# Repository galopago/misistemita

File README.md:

# MISISTEMITA

## ELECTRONIC HARDWARE PROTOTYPING SYSTEM. SOLDERLESS, ROBUST AND OPEN SOURCE

Electronic hardware prototyping system. Solderless, robust and open source. Solves the typical problem of the circuit that works on a breadboard but stops working on a real-world setup. Easy to replicate and compatible with virtually every electronic module.

From this!                     |To this!                              |
-------------------------------|--------------------------------------|
||

Read this in other languages: [Español](/assets/markdown/README.es.md)

The system is completely open source, all the files required to create your own system (schematics, PCB, templates, etc.) are available for download.

### Build a working project in 5 steps:

1.Component selection          |2.Position the components on the backplate |
-------------------------------|-------------------------------------------|
|     |

3.Wire and program           |4.Attach backplate to the enclosure |
-----------------------------|-----------------------------------|
|    |

5.Close lid and install on the wall  |
------------------------------------------|
        |

## System components

The prototyping system is built around 3 key components:
* Backplates
* Electronic boards
* Waterproof enclosures

Backplates                     | Electronic boards                     | Waterproof enclosures       |
-------------------------------|---------------------------------------|---------------------------------------|
| | |

## BACKPLATES

Backplates are flat plates with a distance between holes of 10.16 mm. Backplates are classified as follows: backplates fixed to the enclosure and mechanical adapters for other kinds of modules. The backplates are made in PCB houses, however, they can be built with other materials and processes like laser cutting, CNC machining or homemade with drill and saw!.
[Source files for backplates](/a-backplates)

### Backplates - fixed to the enclosure

This kind of backplates is fixed to the enclosure, all compatible boards are placed on it. The fixing of the backplate to the enclosure is done with self-tapping screws

Backplates - fixed to the enclosure   | 
----------------------------------------------------|
|

### Backplates - mechanical adapter

This kind of adapters are used to convert modules that have mounting holes, but not compatible with 10.16 mm

Backplates - mechanical adapter                      | Backplates - mechanical adapter installed on panel     | 
-----------------------------------------------------|------------------------------------------------------|
||

The distance between holes of 10.16 mm was found after experimentation, using an universal PCB with 2.54 mm space between holes. The 3 mm of diameter was chosen because it is a very  common hole diameter in electronic modules found online)

Distance test between holes 5.08, 7.62 y 10.16mm | Distance test between holes 5.08, 7.62 y 10.16 mm with nuts | 
-----------------------------------------------------|------------------------------------------------------|
||

10.16 mm of distance between holes is a good compromise between compactness and ease of attachment of accessories. Given that the distance of 10.16 mm is an integer multiple of 2.54 mm, these panels could be homebuilt with universal PCB 

Backplate made of universal PCB  | Backplate made of plastic sheet and hand drilled | 
-----------------------------------------------------|------------------------------------------------------|
||

### Fixing elements

Different types of fixing elements for securing boards to backplate |
-----------------------------------------------------|
|

To secure boards to backplate (leaving some gap to avoid shortcuts), there are many possibilities like:

### Nylon spacer, reverse locking without screws

This is a single piece element that allows to attach the boards to the backplate without tools, to detach them a pliers are required

Nylon spacer on board | Board attached to the backplate           | spacer from below  |
---------------------------------|---------------------------------------|---------------------------------------|
| | |

### Nylon spacer with screw and nut

This element is composed of 3 pieces: spacer, screw and nut. A screwdriver is required for fastening and detachment

Nylon spacer with screw on board | Board attached to the backplate             | Nylon spacer with nut from below  |
---------------------------------|---------------------------------------|---------------------------------------|
| | |

### Metal spacer with screw and nut

This element is composed of 3 pieces: spacer, screw and nut. A screwdriver is required for fastening and detachment

Metal spacer with screw on board  | Board attached to the backplate           | Metal spacer with nut from below  |
---------------------------------|---------------------------------------|---------------------------------------|
| | |

## ELECTRONIC BOARDS

Electronic boards are classified as follows:screw terminal connectors, breakouts and active boards. Screw terminals are used as a means of interconnection between all of them, because they work pretty well for solid wire and stranded cable, in addition no crimping is needed. Another good point is that many wires can be attached to the same terminal, very helpful for connecting wire jumpers.

### electronic boards - screw terminal connectors

This type of board is used as a connection point to the external world, organizing in the same spot, sensor inputs, outputs and power sources. Helpful to provide multiple VCC and GND connection points using wire jumpers. They also have holes compatible with 10.16 mm pitch backplates.
[Source files for screw terminal connectors](/b-screw-terminal-wire-connectors)

screw terminal connectors - Different types  |screw terminal connectors - unified spot for cable ingress |  screw terminal connectors - wire diversity|
------------------------|-------------------------------------------------------------|-----------------------------------------------------------|
|| |

### electronic boards - breakouts

This type of board is used to convert DIL style electronic modules into screw terminals, they also have holes compatible with 10.16 mm pitch backplates.
[Source files for breakouts](/c-breakouts)

breakouts - Different types               | breakouts - breakout for Arduino Nano            | breakouts - module as a part of a project |
------------------------------------------|---------------------------------------------------|--------------------------------------------|
|||

### electronic boards - active boards

This type of board has some electrical/electronic component soldered in to do a specific function.
[Source files for active boards](/d-electronics)

electronic boards - Different types       | electronic boards - AC/DC  power supply      | electronic boards - module as a part of a project |
------------------------------------------|---------------------------------------------------|--------------------------------------------|
|||

Same as homebuilt backplates, electronic boards also could be manufactured in a similar fashion, as long as screw terminals were used and mounting holes in increments of 10.16 mm were drilled

homebuilt compatible electronic boards | hybrid project mixing industrial and homebuilt boards | hybrid project installed and working|
------------------------------------------|---------------------------------------------------|--------------------------------------------|
|||

## WATERPROOF ENCLOSURES

The system is based on waterproof enclosures with the following characteristics:
* shall have mounting bosses for the PCB or backplate.
* must be able to be mounted on the wall without drilling the enclosure

### waterproof enclosures - mounting bosses for the PCB using self-tapping screws

The enclosures shall have mounting bosses where the backplate will be attached using self-tapping screws. Those holes usually came pre-drilled and should not break the enclosure

mounting bosses for the PCB |
--------------------------------------------|
|

### waterproof enclosures - wall mount without enclosure drilling

The enclosures must have external mounting ears. There are other kind of boxes that have some holes in the back for mounting purposes, but those holes do not break in the enclosure. In this particular case, some additional accessories will be required.

waterproof enclosures with several wall mounting methods|
-----------------------------------------------------|
               |

waterproof enclosures with mounting ears fixed directly to the wall with screws |
-------------------------------------------------------------------|
                          |

### Fixing accessories

For enclosures with mounting holes in the back, some picture hanging accessories will be handy for mounting them.

Accessories for wall hanging pictures, flat and Z-shaped |
---------------------------------------------------------|
                |

flat hanging accessories | detail of flat hanging accessories  | project using flat hanging accessories for mounting|
------------------------------------------|---------------------------------------------------|--------------------------------------------|
|||

Z-shaped hanging accessories | detail of Z-shaped hanging accessories | project using Z-shaped hanging accessories for mounting|
------------------------------------------|---------------------------------------------------|--------------------------------------------|
|||

### Cable ingress accessories

To avoid moisture and dust infiltration in the enclosure at the cable entry point, this system uses two alternatives:
* Cable glands
* Panel mount connectors

### Cable glands

Cable glands limit the amount of dust and moisture that can enter the enclosure at the cable entry point. Additionally, they provide strain support, avoiding internal disconnections. Cable glands were available in many sizes according to cable thickness. Usually they were used in permanent installations, because the enclosure has to be opened to disconnect the cables.

Different types of cable glands | holes for cable glands installation | Power and signal cables through cable glands|
------------------------------------------|---------------------------------------------------|--------------------------------------------|
|||

### Panel mount connectors

Panel mount connectors limit the amount of dust and moisture that can enter the enclosure at the cable entry point. Additionally, they provide strain support, avoiding internal disconnections.Usually they were used when wires need to be disconnected frequently. Sometimes soldering or crimping is required.

Sample of some types of panel mount connectors | USB-B and aviation panel mount connectors | Power and signal cables through panel mount connectors|
------------------------------------------|---------------------------------------------------|--------------------------------------------|
|||

# Files and additional info:

| DESCRIPTION                                                     | LINK                                   
|-----------------------------------------------------------------|----------------------------------------------------------------------
| Source files for backplates                                     | [Backplates](/a-backplates)
| Source files for screw terminal connectors                      | [Screw terminal connectors](/b-screw-terminal-wire-connectors)
| Source files for breakouts                                      | [Breakout](/c-breakouts)
| Source files for active boards                                  | [Active boards](/d-electronics)
| Complete finished examples using Misistemita                    | [Galopago](https://galopago.github.io)

Misistemita is an open source project by [Galopago](https://galopago.github.io/)

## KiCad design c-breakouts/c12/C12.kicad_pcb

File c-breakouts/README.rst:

=======================================================================================================================================
TUSISTEMITA TYPE-C BOARDS: BREAKOUTS
=======================================================================================================================================

Breakout for converting electronic modules, to screw terminal connectors and 10.16 mm hole spacing

Directory structure of every board folder
--------------------------------------------------------------------------
* The root contains KiCad files: project, schematic and PCB.
* gerber/single directory contains ready to manufacture files, for a single board.
* gerber/panel_100mmx100mm directory contains ready to manufacture files that fits in a 100mm x 100mm panel (use Vcuts!).

========  ===============  ============== 
FOLDER    PCB MARK         DESCRIPTION
========  ===============  ============== 
C00       C00_BREAKOUT     Breakout for power meter PZEM-004T-100A (V3.0)
C01       C01_BREAKOUT     Breakout for RAK811 LoRa breakboard
C02       C02_BREAKOUT     Breakout for RAK4200 LoRa breakboard
C03       C03_BREAKOUT     Breakout for 2xAA R6 type batteries
C04       C04_BREAKOUT     Breakout for Arduino Nano
C05       C05_BREAKOUT     Breakout for Raspberry Pi 40 pin (2x20) header
C06       C06_BREAKOUT     Breakout for 21 mm x 23 mm prototyping area
C07       C07_BREAKOUT     Breakout for ESP32 devboards with 38 pins (2x19 2.54mm pitch) or less and 25,4 mm separation between headers  
C08       C08_BREAKOUT     Breakout for ESP8266 devboards with 30 pins (2x15 2.54mm pitch) or less and ( 22,86 or 27.94mm ) separation between headers  
C09       C09_BREAKOUT     Breakout for USB A Male (USB A Female connected to screw terminals) power pins
C10       C10_BREAKOUT     Breakout for 0.96" OLED 4 pin I2C display
C11       C11_BREAKOUT     Breakout for Raspberry Pi Pico Board
C12       C12_BREAKOUT     Breakout for ESP32 Cam Board
C13       C13_BREAKOUT     Breakout for 18 pin (2x9) header
========  ===============  ==============

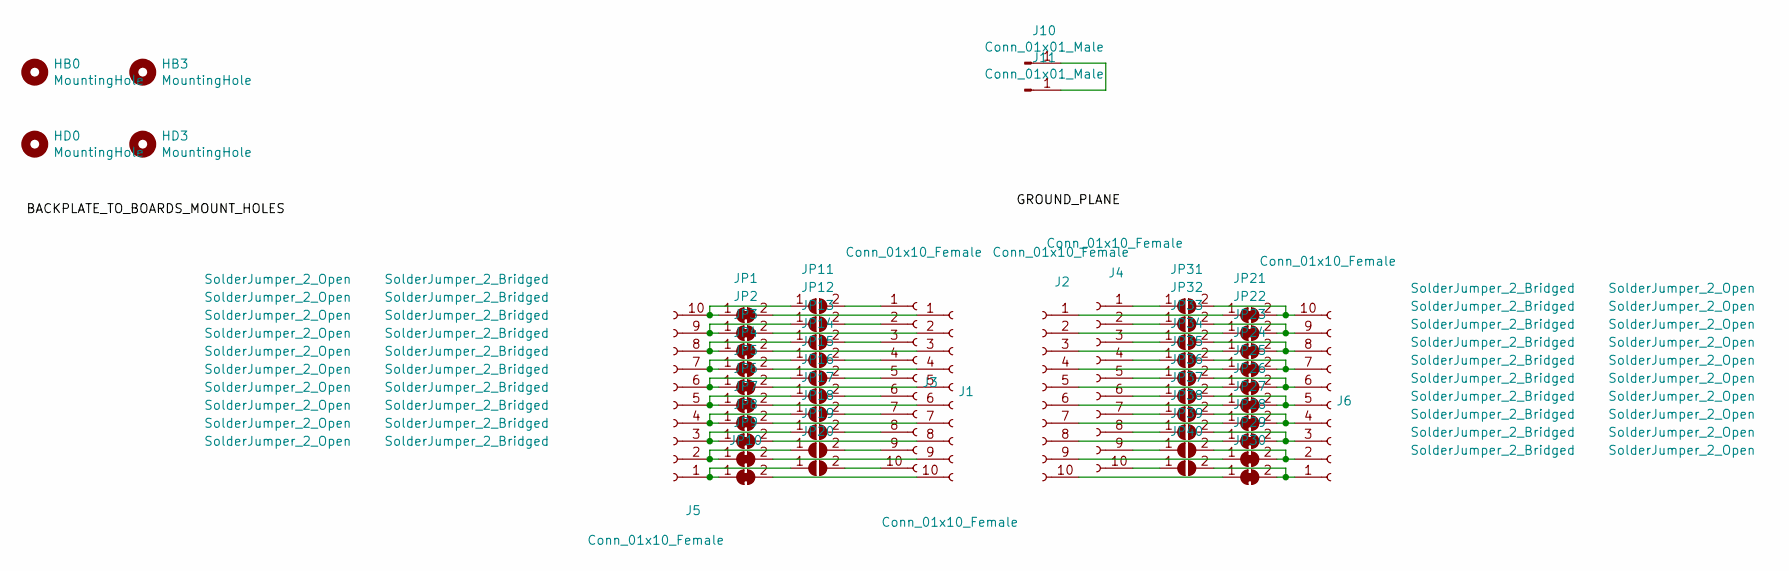
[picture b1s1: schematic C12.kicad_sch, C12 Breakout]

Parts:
HB0, HB3: MountingHole; MountingHole_3mm
HD0, HD3: MountingHole; MountingHole_3mm
J1, J2, J3, J4: Conn_01x10_Female; PinHeader_1x10_P2.54mm_Vertical
J5, J6: Conn_01x10_Female; TerminalBlock_4Ucon_1x10_P3.50mm_Vertical
J10, J11: Conn_01x01_Male; SolderWirePad_1x01_Drill1mm
JP1, JP2, JP3, JP4, JP5, JP6, JP7, JP8, JP9, JP10, JP21, JP22, JP23, JP24, JP25, JP26, JP27, JP28, JP29, JP30: SolderJumper_2_Bridged; SolderJumper-2_P1.3mm_Bridged_RoundedPad1.0x1.5mm
JP11, JP12, JP13, JP14, JP15, JP16, JP17, JP18, JP19, JP20, JP31, JP32, JP33, JP34, JP35, JP36, JP37, JP38, JP39, JP40: SolderJumper_2_Open; SolderJumper-2_P1.3mm_Open_RoundedPad1.0x1.5mm

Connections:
unnamed: J1.1, JP1.2 (B)
unnamed: J1.2, JP2.2 (B)
unnamed: J1.3, JP3.2 (B)
unnamed: J1.4, JP4.2 (B)
unnamed: J1.5, JP5.2 (B)
unnamed: J1.6, JP6.2 (B)
unnamed: J1.7, JP7.2 (B)
unnamed: J1.8, JP8.2 (B)
unnamed: J1.9, JP9.2 (B)
unnamed: J1.10, JP10.2 (B)
unnamed: J2.1, JP21.1 (A)
unnamed: J2.2, JP22.1 (A)
unnamed: J2.3, JP23.1 (A)
unnamed: J2.4, JP24.1 (A)
unnamed: J2.5, JP25.1 (A)
unnamed: J2.6, JP26.1 (A)
unnamed: J2.7, JP27.1 (A)
unnamed: J2.8, JP28.1 (A)
unnamed: J2.9, JP29.1 (A)
unnamed: J2.10, JP30.1 (A)
unnamed: J3.1, JP11.2 (B)
unnamed: J3.2, JP12.2 (B)
unnamed: J3.3, JP13.2 (B)
unnamed: J3.4, JP14.2 (B)
unnamed: J3.5, JP15.2 (B)
unnamed: J3.6, JP16.2 (B)
unnamed: J3.7, JP17.2 (B)
unnamed: J3.8, JP18.2 (B)
unnamed: J3.9, JP19.2 (B)
unnamed: J3.10, JP20.2 (B)
unnamed: J4.1, JP31.1 (A)
unnamed: J4.2, JP32.1 (A)
unnamed: J4.3, JP33.1 (A)
unnamed: J4.4, JP34.1 (A)
unnamed: J4.5, JP35.1 (A)
unnamed: J4.6, JP36.1 (A)
unnamed: J4.7, JP37.1 (A)
unnamed: J4.8, JP38.1 (A)
unnamed: J4.9, JP39.1 (A)
unnamed: J4.10, JP40.1 (A)
unnamed: J10.1, J11.1
unnamed: J5.10, JP1.1 (A), JP11.1 (A)
unnamed: J5.1, JP10.1 (A), JP20.1 (A)
unnamed: J5.9, JP2.1 (A), JP12.1 (A)
unnamed: J5.8, JP3.1 (A), JP13.1 (A)
unnamed: J5.7, JP4.1 (A), JP14.1 (A)
unnamed: J5.6, JP5.1 (A), JP15.1 (A)
unnamed: J5.5, JP6.1 (A), JP16.1 (A)
unnamed: J5.4, JP7.1 (A), JP17.1 (A)
unnamed: J5.3, JP8.1 (A), JP18.1 (A)
unnamed: J5.2, JP9.1 (A), JP19.1 (A)
unnamed: J6.10, JP21.2 (B), JP31.2 (B)
unnamed: J6.9, JP22.2 (B), JP32.2 (B)
unnamed: J6.8, JP23.2 (B), JP33.2 (B)
unnamed: J6.7, JP24.2 (B), JP34.2 (B)
unnamed: J6.6, JP25.2 (B), JP35.2 (B)
unnamed: J6.5, JP26.2 (B), JP36.2 (B)
unnamed: J6.4, JP27.2 (B), JP37.2 (B)
unnamed: J6.3, JP28.2 (B), JP38.2 (B)
unnamed: J6.2, JP29.2 (B), JP39.2 (B)
unnamed: J6.1, JP30.2 (B), JP40.2 (B)

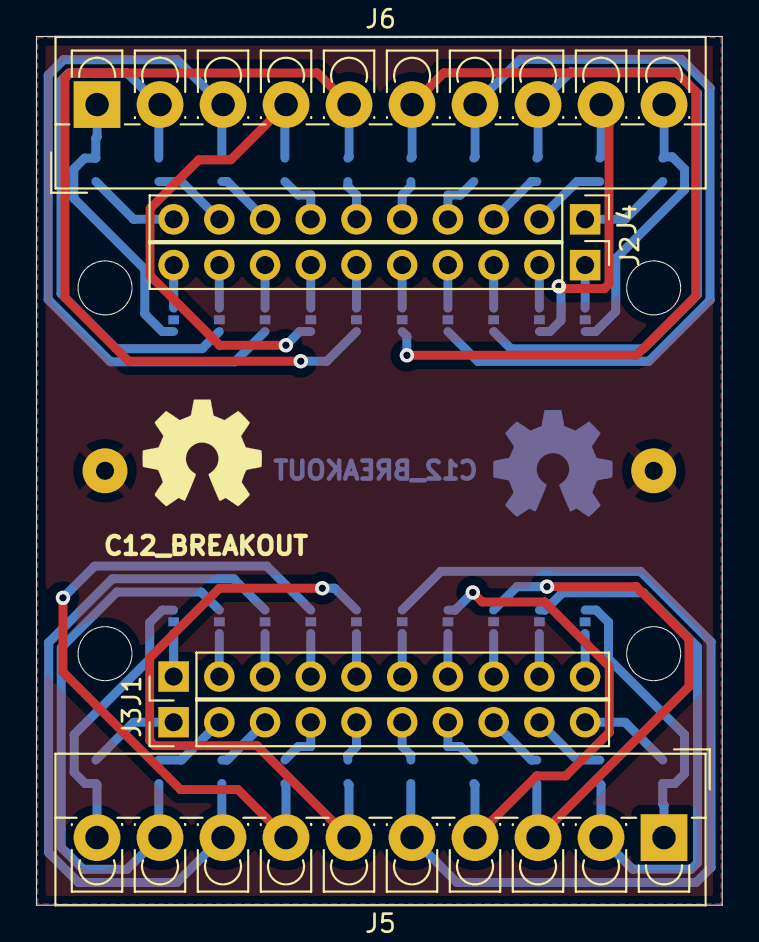
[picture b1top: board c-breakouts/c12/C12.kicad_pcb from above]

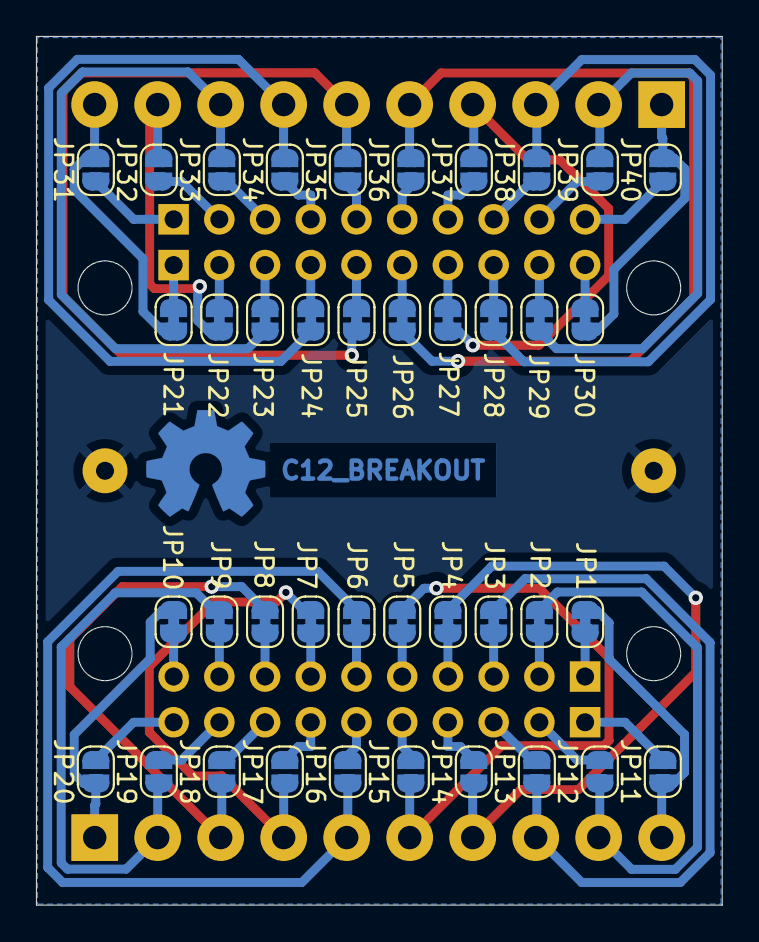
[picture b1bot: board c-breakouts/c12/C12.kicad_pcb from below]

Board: 2 copper layers, 38.1 x 48.3 mm, 54 parts (41 on the bottom side), 61 nets.

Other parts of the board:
REFS0**: OSHW-Symbol_6.7x6mm_Copper
REFS1**: OSHW-Symbol_6.7x6mm_SilkScreen

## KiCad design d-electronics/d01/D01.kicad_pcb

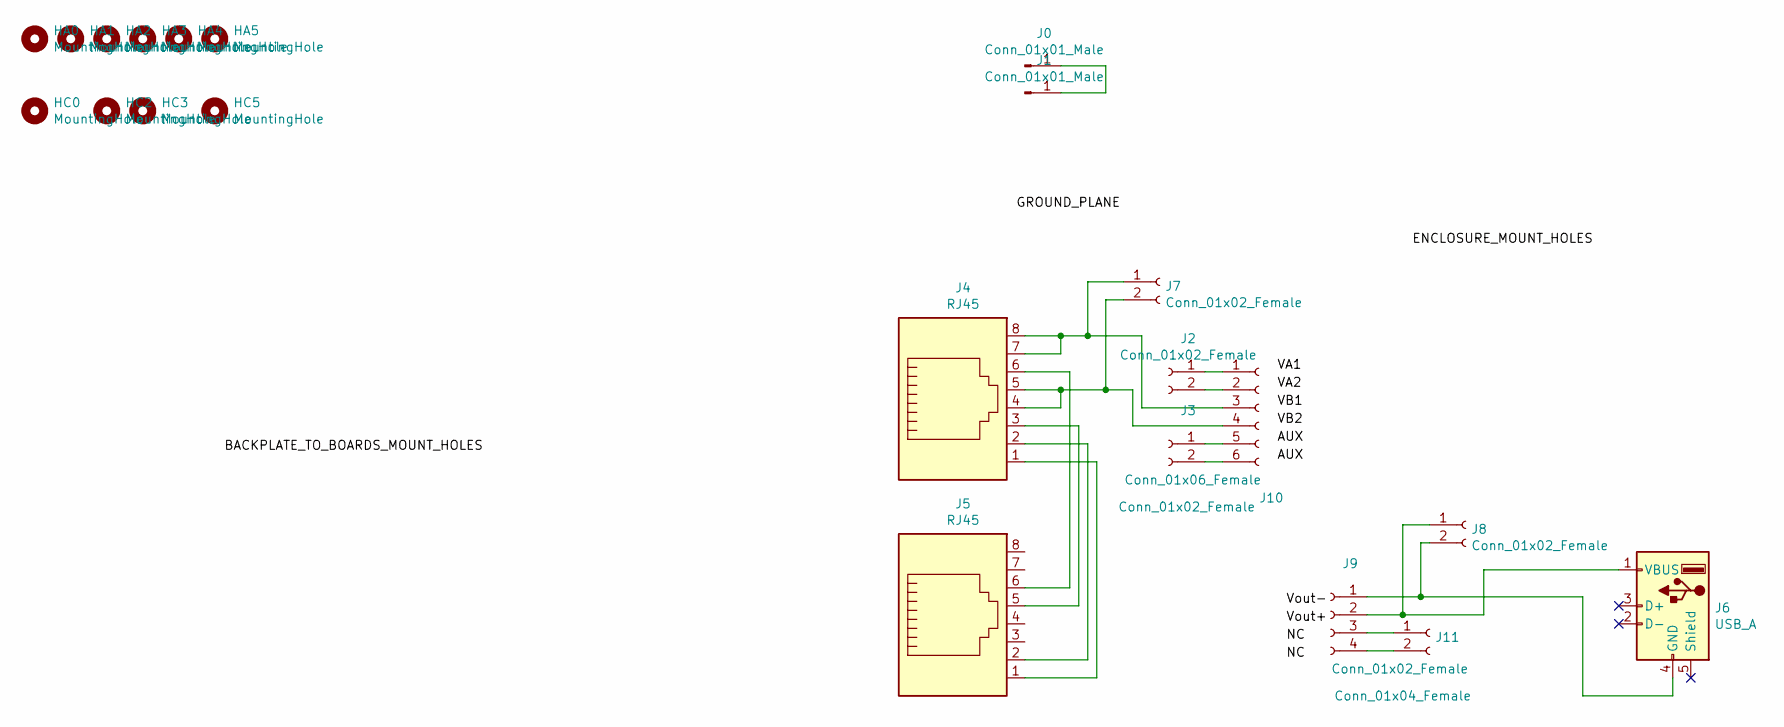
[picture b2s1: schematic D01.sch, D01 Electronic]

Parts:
HA0, HA1, HA2, HA3, HA4, HA5: MountingHole; MountingHole_3mm
HC0, HC2, HC3, HC5: MountingHole; MountingHole_3mm
J0, J1: Conn_01x01_Male; SolderWirePad_1x01_Drill1mm
J2, J3, J11: Conn_01x02_Female; PinSocket_1x02_P2.54mm_Vertical
J4, J5: RJ45; RJ45_Wayconn_MJEA-880X1_Horizontal
J6: USB_A; USB_A_Stewart_SS-52100-001_Horizontal
J7, J8: Conn_01x02_Female; TerminalBlock_4Ucon_1x02_P3.50mm_Horizontal
J9: Conn_01x04_Female; PinSocket_1x04_P2.54mm_Vertical
J10: Conn_01x06_Female; PinSocket_1x06_P2.54mm_Vertical

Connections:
unnamed: J0.1, J1.1
unnamed: J4.1, J5.1
unnamed: J4.2, J5.2
unnamed: J4.3, J5.5
unnamed: J4.6, J5.6
unnamed: J6.1 (VBUS), J8.1, J9.2
unnamed: J6.4 (GND), J8.2, J9.1
unnamed: J2.1, J10.1
unnamed: J2.2, J10.2
unnamed: J4.7, J4.8, J7.1, J10.3
unnamed: J4.4, J4.5, J7.2, J10.4
unnamed: J3.1, J10.5
unnamed: J3.2, J10.6
unnamed: J9.3, J11.1
unnamed: J9.4, J11.2

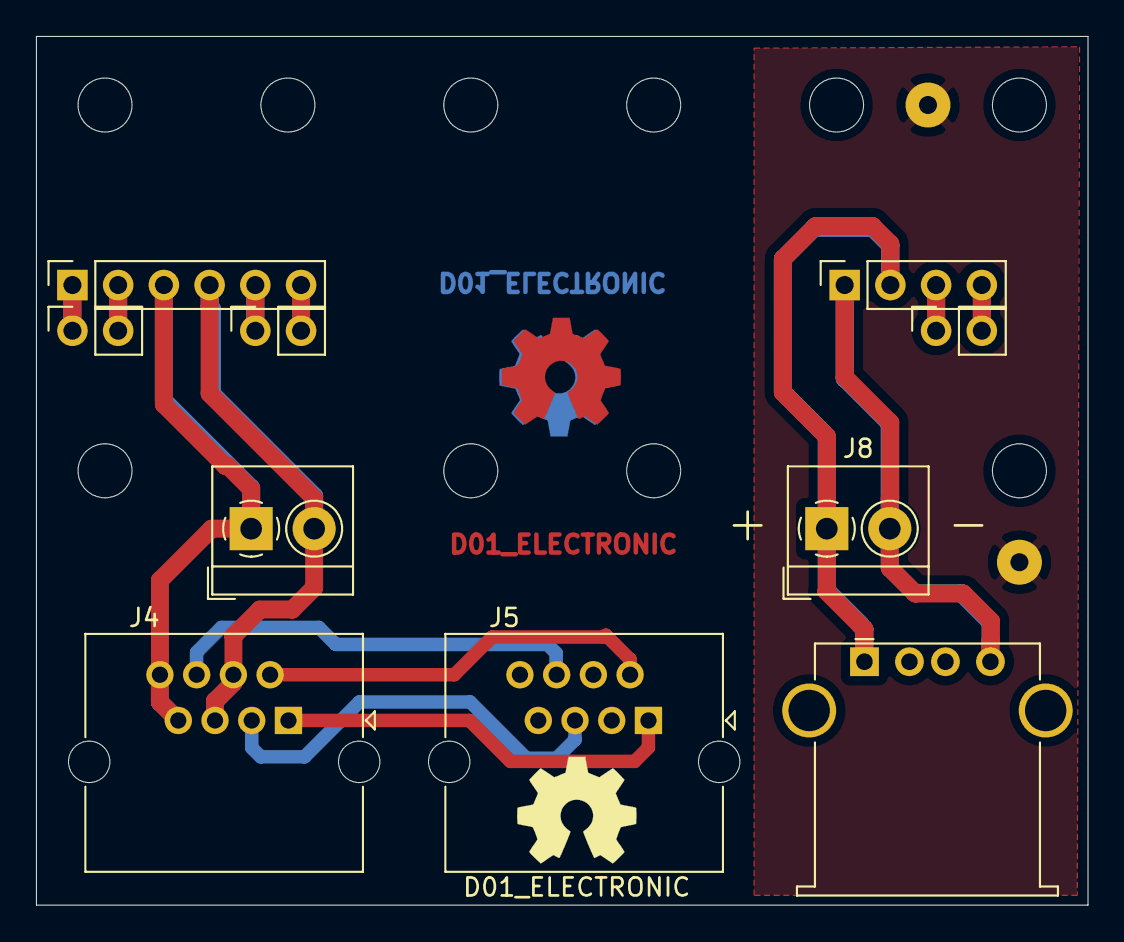
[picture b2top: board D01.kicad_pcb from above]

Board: 2 copper layers, 58.4 x 48.3 mm, 22 parts (0 on the bottom side), 15 nets.

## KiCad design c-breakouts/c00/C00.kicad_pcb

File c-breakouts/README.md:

# MISISTEMITA TYPE-C BOARDS: BREAKOUTS

Breakout for converting electronic modules, to screw terminal connectors and 10.16 mm hole spacing

Different breakout boards                                           |
------------------------------------------------------------------------------------|
|

## Directory structure of every board folder

* The root contains KiCad files: project, schematic and PCB.
* gerber/single directory contains ready to manufacture files, for a single board.
* gerber/panel_100mmx100mm directory contains ready to manufacture files that fits in a 100mm x 100mm panel (use Vcuts!).
* assets folder contains support files for readme.md

| DESCRIPTION                                    | PCB MARK     | LINK                                     
|------------------------------------------------|--------------|------
| Breakout for power meter PZEM-004T-100A (V3.0) | C00_BREAKOUT | [c00](/c-breakouts/c00)
| Breakout for RAK811 LoRa breakboard            | C01_BREAKOUT | [c01](/c-breakouts/c01)
| Breakout for RAK4200 LoRa breakboard           | C02_BREAKOUT | [c02](/c-breakouts/c02)
| Breakout for 2xAA R6 type batteries            | C03_BREAKOUT | [c03](/c-breakouts/c03)
| Breakout for Arduino Nano                      | C04_BREAKOUT | [c04](/c-breakouts/c04)
| Breakout for Raspberry Pi 40 pin (2x20) header | C05_BREAKOUT | [c05](/c-breakouts/c05)
| Breakout for 21 mm x 23 mm prototyping area    | C06_BREAKOUT | [c06](/c-breakouts/c06)
| Breakout for ESP32 devboards with 38 pins (2x19 2.54mm pitch) or less and 25,4 mm separation between headers                | C07_BREAKOUT | [c07](/c-breakouts/c07) 
| Breakout for ESP8266 devboards with 30 pins (2x15 2.54mm pitch) or less and ( 22,86 or 27.94mm ) separation between headers | C08_BREAKOUT | [c08](/c-breakouts/c08)
| Breakout for USB A Male (USB A Female connected to screw terminals) power pins | C09_BREAKOUT | [c09](/c-breakouts/c09)
| Breakout for 0.96" OLED 4 pin I2C display      | C10_BREAKOUT | [c10](/c-breakouts/c10)
| Breakout for Raspberry Pi Pico Board           | C11_BREAKOUT | [c11](/c-breakouts/c11)
| Breakout for ESP32 Cam Board                   | C12_BREAKOUT | [c12](/c-breakouts/c12)
| Breakout for 18 pin (2x9) header               | C13_BREAKOUT | [c13](/c-breakouts/c13)

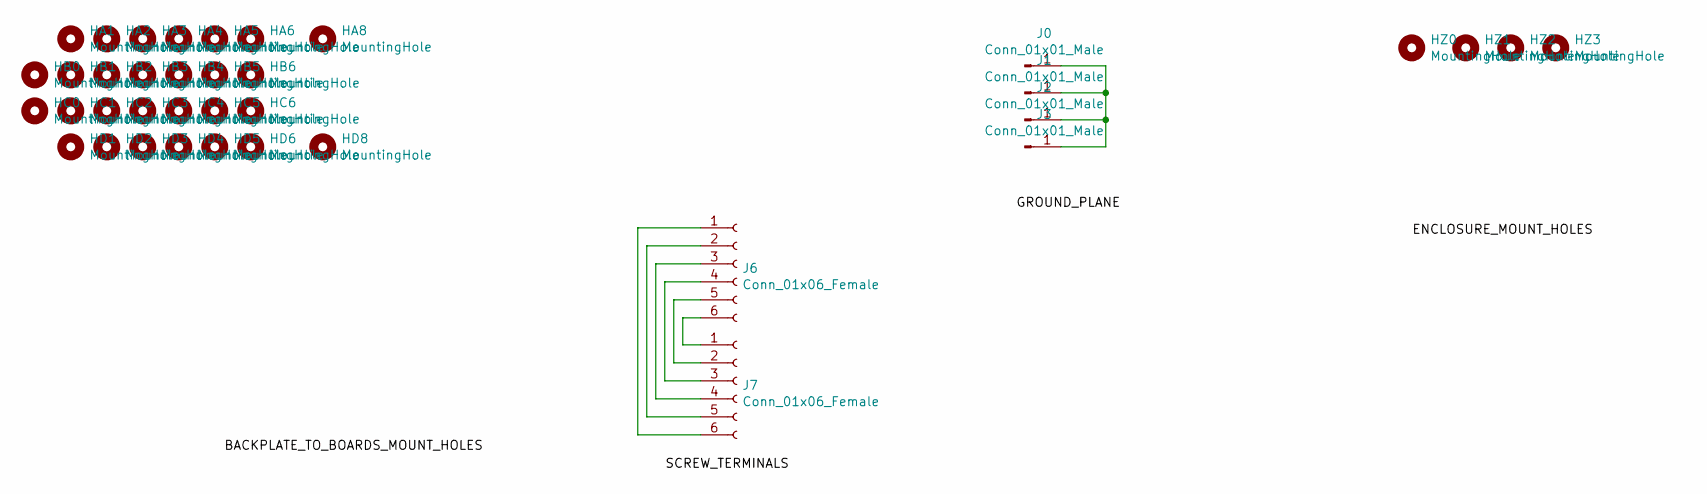
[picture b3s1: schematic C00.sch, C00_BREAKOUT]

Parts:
HA1, HA2, HA3, HA4, HA5, HA6, HA8: MountingHole; MountingHole_3mm
HB0, HB1, HB2, HB3, HB4, HB5, HB6: MountingHole; MountingHole_3mm
HC0, HC1, HC2, HC3, HC4, HC5, HC6: MountingHole; MountingHole_3mm
HD1, HD2, HD3, HD4, HD5, HD6, HD8: MountingHole; MountingHole_3mm
HZ0, HZ1, HZ2, HZ3: MountingHole; MountingHole_3mm
J0, J1, J2, J3: Conn_01x01_Male; SolderWirePad_1x01_Drill1mm
J6, J7: Conn_01x06_Female; TerminalBlock_4Ucon_1x06_P3.50mm_Horizontal

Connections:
unnamed: J0.1, J1.1, J2.1, J3.1
unnamed: J6.1, J7.6
unnamed: J6.2, J7.5
unnamed: J6.3, J7.4
unnamed: J6.4, J7.3
unnamed: J6.5, J7.2
unnamed: J6.6, J7.1

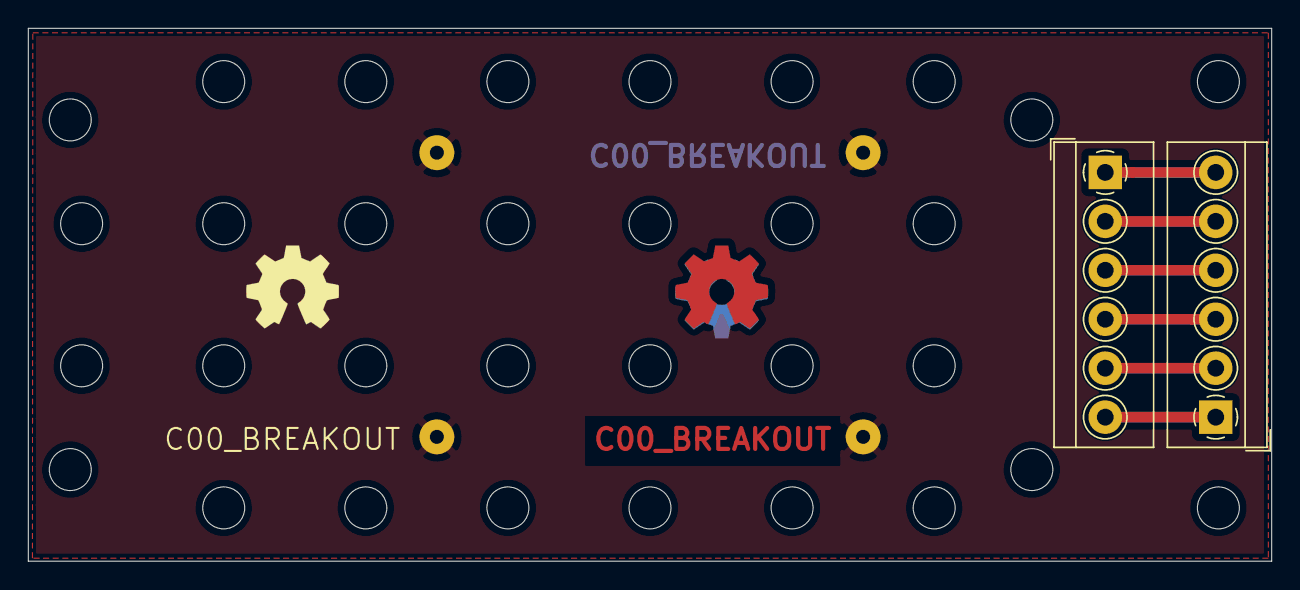
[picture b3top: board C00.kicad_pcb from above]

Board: 2 copper layers, 88.9 x 38.1 mm, 38 parts (0 on the bottom side), 7 nets.

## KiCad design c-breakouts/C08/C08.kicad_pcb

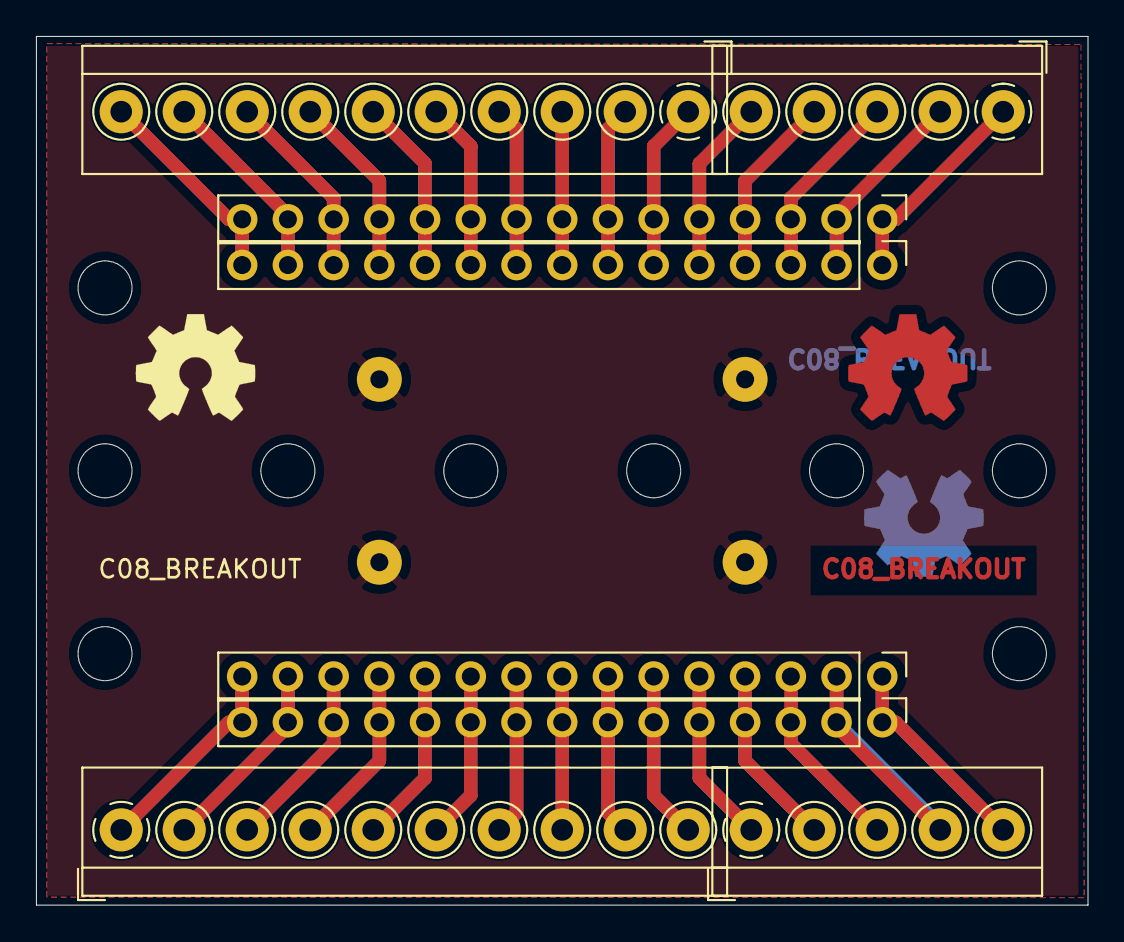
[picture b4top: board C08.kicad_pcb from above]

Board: 2 copper layers, 58.4 x 48.3 mm, 22 parts (0 on the bottom side), 31 nets.

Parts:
HB0, HB6: MountingHole; MountingHole_3mm
HC0, HC1, HC2, HC3, HC4, HC5: MountingHole; MountingHole_3mm
HD0, HD6: MountingHole; MountingHole_3mm
J0, J1, J2, J3: Conn_01x01_Male; SolderWirePad_1x01_Drill1mm
J4, J6: Conn_01x10_Female; TerminalBlock_4Ucon_1x10_P3.50mm_Horizontal
J5, J7: Conn_01x05_Female; TerminalBlock_4Ucon_1x05_P3.50mm_Horizontal
J8, J9, J10, J11: Conn_01x15_Female; PinHeader_1x15_P2.54mm_Vertical

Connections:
unnamed: J0.1, J1.1, J2.1, J3.1
unnamed: J5.1, J8.1, J10.1
unnamed: J5.2, J8.2, J10.2
unnamed: J5.3, J8.3, J10.3
unnamed: J5.4, J8.4, J10.4
unnamed: J5.5, J8.5, J10.5
unnamed: J4.1, J8.6, J10.6
unnamed: J4.2, J8.7, J10.7
unnamed: J4.3, J8.8, J10.8
unnamed: J4.4, J8.9, J10.9
unnamed: J4.5, J8.10, J10.10
unnamed: J4.6, J8.11, J10.11
unnamed: J4.7, J8.12, J10.12
unnamed: J4.8, J8.13, J10.13
unnamed: J4.9, J8.14, J10.14
unnamed: J4.10, J8.15, J10.15
unnamed: J7.5, J9.1, J11.1
unnamed: J7.4, J9.2, J11.2
unnamed: J7.3, J9.3, J11.3
unnamed: J7.2, J9.4, J11.4
unnamed: J7.1, J9.5, J11.5
unnamed: J6.10, J9.6, J11.6
unnamed: J6.9, J9.7, J11.7
unnamed: J6.8, J9.8, J11.8
unnamed: J6.7, J9.9, J11.9
unnamed: J6.6, J9.10, J11.10
unnamed: J6.5, J9.11, J11.11
unnamed: J6.4, J9.12, J11.12
unnamed: J6.3, J9.13, J11.13
unnamed: J6.2, J9.14, J11.14
unnamed: J6.1, J9.15, J11.15

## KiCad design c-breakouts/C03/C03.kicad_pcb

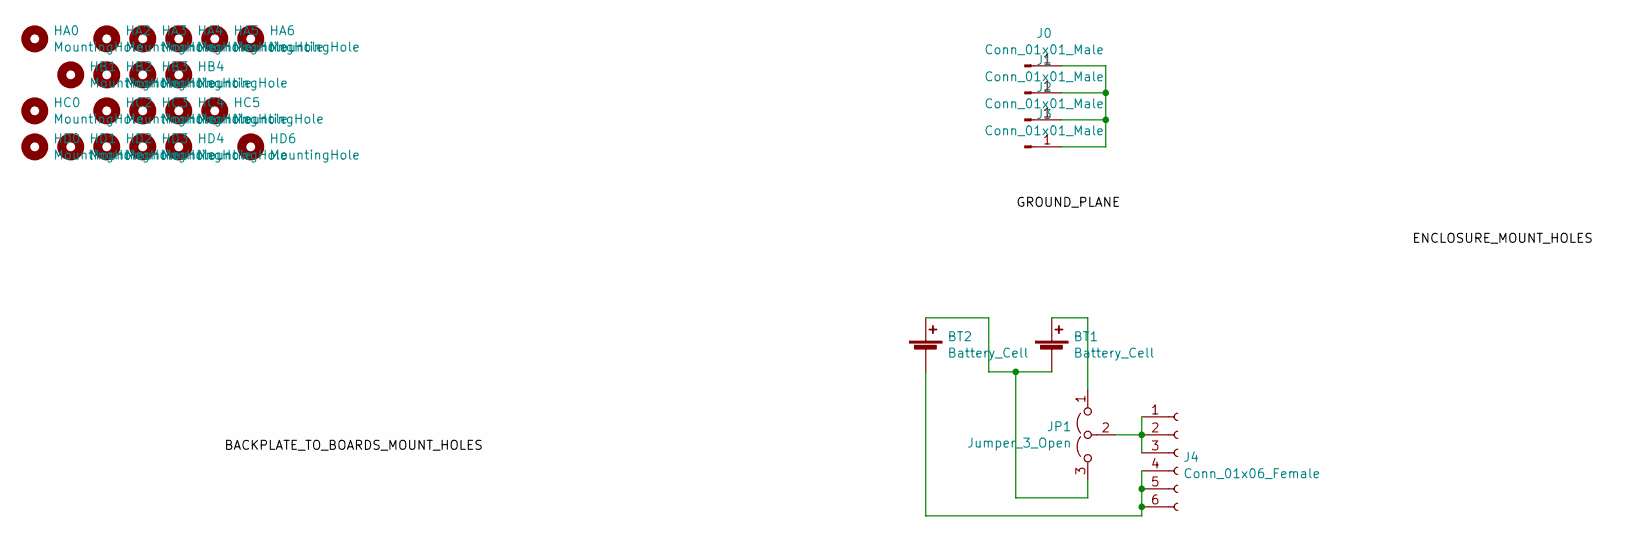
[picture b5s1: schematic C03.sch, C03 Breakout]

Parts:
BT1, BT2: Battery_Cell; BatteryHolder_Keystone_2460_1xAA
HA0, HA2, HA3, HA4, HA5, HA6: MountingHole; MountingHole_3mm
HB1, HB2, HB3, HB4: MountingHole; MountingHole_3mm
HC0, HC2, HC3, HC4, HC5: MountingHole; MountingHole_3mm
HD0, HD1, HD2, HD3, HD4, HD6: MountingHole; MountingHole_3mm
J0, J1, J2, J3: Conn_01x01_Male; SolderWirePad_1x01_Drill1mm
J4: Conn_01x06_Female; TerminalBlock_4Ucon_1x06_P3.50mm_Horizontal
JP1: Jumper_3_Open; PinHeader_1x03_P2.54mm_Vertical

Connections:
unnamed: BT1.1 (+), JP1.1 (A)
unnamed: BT1.2 (-), BT2.1 (+), JP1.3 (B)
unnamed: BT2.2 (-), J4.4, J4.5, J4.6
unnamed: J0.1, J1.1, J2.1, J3.1
unnamed: J4.1, J4.2, J4.3, JP1.2 (C)

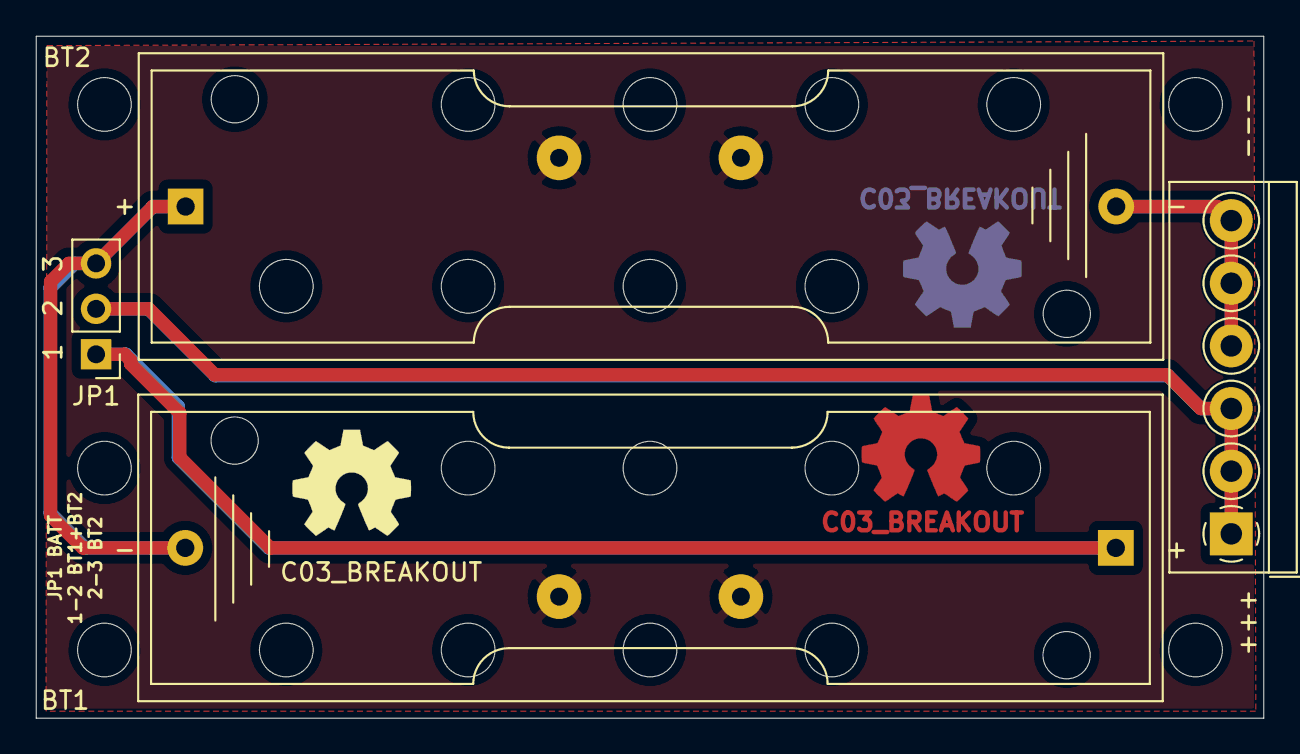
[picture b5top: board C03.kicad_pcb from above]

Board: 2 copper layers, 68.6 x 38.1 mm, 29 parts (0 on the bottom side), 5 nets.

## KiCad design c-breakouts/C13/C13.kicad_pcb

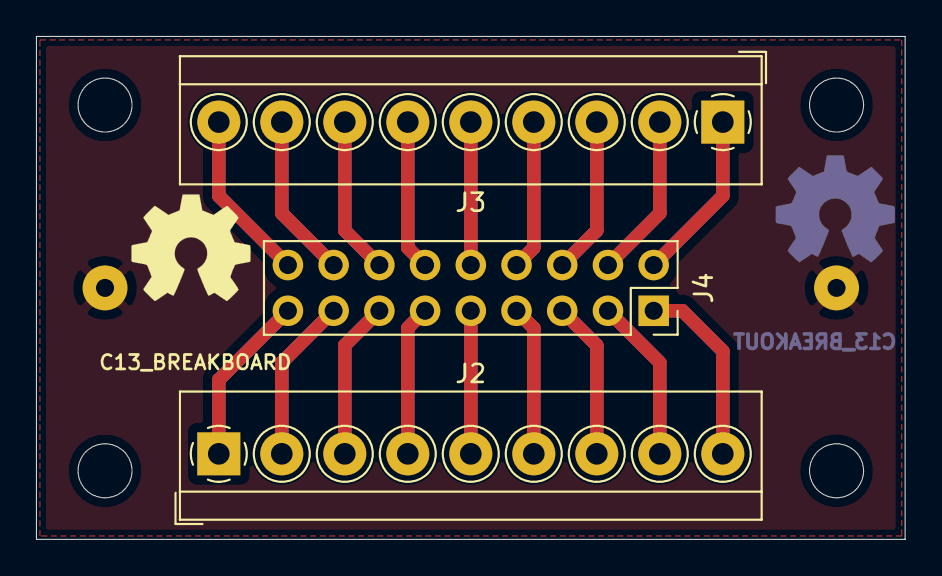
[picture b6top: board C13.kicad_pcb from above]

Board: 2 copper layers, 48.3 x 27.9 mm, 9 parts (0 on the bottom side), 19 nets.

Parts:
HA0, HA4: MountingHole; MountingHole_3mm
HB0, HB4: MountingHole; MountingHole_3mm
J0, J1: Conn_01x01_Male; SolderWirePad_1x01_Drill1mm
J2, J3: Conn_01x09_Female; TerminalBlock_4Ucon_1x09_P3.50mm_Horizontal
J4: Conn_02x09_Odd_Even; PinSocket_2x09_P2.54mm_Vertical

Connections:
unnamed: J0.1, J1.1
unnamed: J2.1, J4.17
unnamed: J2.2, J4.15
unnamed: J2.3, J4.13
unnamed: J2.4, J4.11
unnamed: J2.5, J4.9
unnamed: J2.6, J4.7
unnamed: J2.7, J4.5
unnamed: J2.8, J4.3
unnamed: J2.9, J4.1
unnamed: J3.1, J4.2
unnamed: J3.2, J4.4
unnamed: J3.3, J4.6
unnamed: J3.4, J4.8
unnamed: J3.5, J4.10
unnamed: J3.6, J4.12
unnamed: J3.7, J4.14
unnamed: J3.8, J4.16
unnamed: J3.9, J4.18

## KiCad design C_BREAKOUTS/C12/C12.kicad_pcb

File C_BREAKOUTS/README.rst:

=======================================================================================================================================
TUSISTEMITA TYPE-C BOARDS: BREAKOUTS
=======================================================================================================================================

Breakout for converting electronic modules, to screw terminal connectors and 10.16 mm hole spacing

Directory structure of every board folder
--------------------------------------------------------------------------
* The root contains KiCad files: project, schematic and PCB.
* gerber/single directory contains ready to manufacture files, for a single board.
* gerber/panel_100mmx100mm directory contains ready to manufacture files that fits in a 100mm x 100mm panel (use Vcuts!).

========  ===============  ============== 
FOLDER    PCB MARK         DESCRIPTION
========  ===============  ============== 
C00       C00_BREAKOUT     Breakout for power meter PZEM-004T-100A (V3.0)
C01       C01_BREAKOUT     Breakout for RAK811 LoRa breakboard
C02       C02_BREAKOUT     Breakout for RAK4200 LoRa breakboard
C03       C03_BREAKOUT     Breakout for 2xAA R6 type batteries
C04       C04_BREAKOUT     Breakout for Arduino Nano
C05       C05_BREAKOUT     Breakout for Raspberry Pi 40 pin (2x20) header
C06       C06_BREAKOUT     Breakout for 21 mm x 23 mm prototyping area
C07       C07_BREAKOUT     Breakout for ESP32 devboards with 38 pins (2x19 2.54mm pitch) or less and 25,4 mm separation between headers  
C08       C08_BREAKOUT     Breakout for ESP8266 devboards with 30 pins (2x15 2.54mm pitch) or less and ( 22,86 or 27.94mm ) separation between headers  
C09       C09_BREAKOUT     Breakout for USB A Male (USB A Female connected to screw terminals) power pins
C10       C10_BREAKOUT     Breakout for 0.96" OLED 4 pin I2C display
C11       C11_BREAKOUT     Breakout for Raspberry Pi Pico Board
C12       C12_BREAKOUT     Breakout for ESP32 Cam Board
========  ===============  ==============

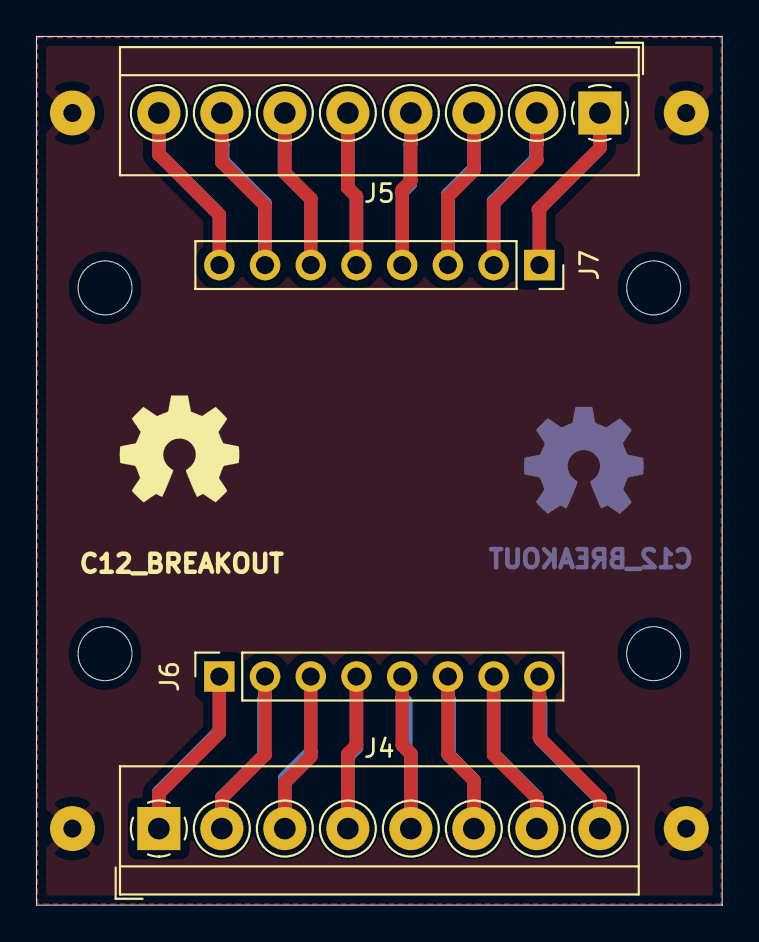
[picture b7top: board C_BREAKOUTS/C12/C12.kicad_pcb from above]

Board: 2 copper layers, 38.1 x 48.3 mm, 12 parts (0 on the bottom side), 17 nets.

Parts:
HB0, HB3: MountingHole; MountingHole_3mm
HD0, HD3: MountingHole; MountingHole_3mm
J0, J1, J2, J3: Conn_01x01_Male; SolderWirePad_1x01_Drill1mm
J4, J5: Conn_01x08_Female; TerminalBlock_4Ucon_1x08_P3.50mm_Horizontal
J6, J7: Conn_01x08_Female; PinSocket_1x08_P2.54mm_Vertical

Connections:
unnamed: J0.1, J1.1, J2.1, J3.1
unnamed: J4.1, J6.1
unnamed: J4.2, J6.2
unnamed: J4.3, J6.3
unnamed: J4.4, J6.4
unnamed: J4.5, J6.5
unnamed: J4.6, J6.6
unnamed: J4.7, J6.7
unnamed: J4.8, J6.8
unnamed: J5.1, J7.1
unnamed: J5.2, J7.2
unnamed: J5.3, J7.3
unnamed: J5.4, J7.4
unnamed: J5.5, J7.5
unnamed: J5.6, J7.6
unnamed: J5.7, J7.7
unnamed: J5.8, J7.8

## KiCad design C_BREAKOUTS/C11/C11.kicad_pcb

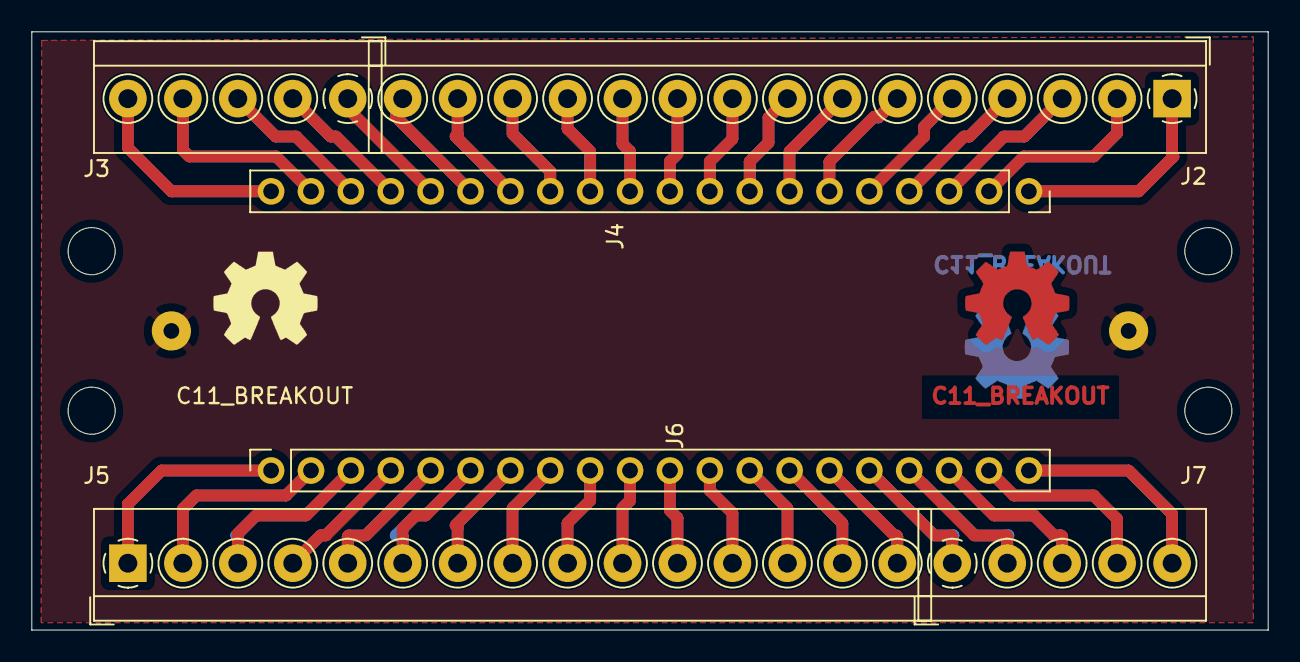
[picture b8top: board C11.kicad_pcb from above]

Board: 2 copper layers, 78.7 x 38.1 mm, 12 parts (0 on the bottom side), 41 nets.

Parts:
HB0, HB5: MountingHole; MountingHole_3mm
HC0, HC5: MountingHole; MountingHole_3mm
J0, J1: Conn_01x01_Male; SolderWirePad_1x01_Drill1mm
J2, J5: Conn_01x15_Female; TerminalBlock_4Ucon_1x15_P3.50mm_Horizontal
J3, J7: Conn_01x05_Female; TerminalBlock_4Ucon_1x05_P3.50mm_Horizontal
J4, J6: Conn_01x20_Female; PinSocket_1x20_P2.54mm_Vertical

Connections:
unnamed: J0.1, J1.1
unnamed: J2.1, J4.1
unnamed: J2.2, J4.2
unnamed: J2.3, J4.3
unnamed: J2.4, J4.4
unnamed: J2.5, J4.5
unnamed: J2.6, J4.6
unnamed: J2.7, J4.7
unnamed: J2.8, J4.8
unnamed: J2.9, J4.9
unnamed: J2.10, J4.10
unnamed: J2.11, J4.11
unnamed: J2.12, J4.12
unnamed: J2.13, J4.13
unnamed: J2.14, J4.14
unnamed: J2.15, J4.15
unnamed: J3.1, J4.16
unnamed: J3.2, J4.17
unnamed: J3.3, J4.18
unnamed: J3.4, J4.19
unnamed: J3.5, J4.20
unnamed: J5.1, J6.1
unnamed: J5.2, J6.2
unnamed: J5.3, J6.3
unnamed: J5.4, J6.4
unnamed: J5.5, J6.5
unnamed: J5.6, J6.6
unnamed: J5.7, J6.7
unnamed: J5.8, J6.8
unnamed: J5.9, J6.9
unnamed: J5.10, J6.10
unnamed: J5.11, J6.11
unnamed: J5.12, J6.12
unnamed: J5.13, J6.13
unnamed: J5.14, J6.14
unnamed: J5.15, J6.15
unnamed: J6.16, J7.1
unnamed: J6.17, J7.2
unnamed: J6.18, J7.3
unnamed: J6.19, J7.4
unnamed: J6.20, J7.5
